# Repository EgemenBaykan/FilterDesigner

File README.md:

<h1><b>Filter Designer</b></h1>

<p>Filter Designer is a console program that designs 4 basic filters for given inputs. It is written in Python and Jupyter Notebook will be available soon. It is not recommended to use frequencies above 200-300 MHz since wavelength decreases in lumped element model filters. Use distributed element model for higher frequencies.</p>

<p>Filters are circuits that can pass or stop given frequencies or frequency bands. Passive filters contain passive elements unlike active filters. These elements are resistors, capacitors and inductors. Resistor is not a good practice in RF circuits. Therefore inductors are used instead of resistors since they boost the current.</p>

<p>In practice, passive filters are designed by using <b>Normalized Filter Coefficient Tables</b>. Filter order and characteristic are determined by performance requirements. This is, usually, done by providing attenuation on unwanted frequency components. Bode plots are used to analyze frequency response of RF circuits such as filters and magnitude is in <b>Decibel (dB)</b> scale.</p>

<h3><b>Program Inputs</b></h3>

<p> Basically there are 5 types of program inputs. These inputs are explained as follow:</p>

<ol>
    <li> <b>Filter Type:</b> </li>
    <ul>
        <li><b>LPF:</b> Defines Low Pass Filter.</li>
        <li><b>HPF:</b> Defines High Pass Filter.</li>
        <li><b>BPF:</b> Defines Band Pass Filter.</li>
        <li><b>BSF:</b> Defines Band Stop Filter.</li>
    </ul>
    <li> <b>Cutoff Frequency:</b> Defines -3dB point(s) of the filter. Low and high cutoff frequencies are given as inputs for Bandpass Filter or Bandstop Filter. Scientific notation is used for cutoff frequencies in Hz.</li>
    <li> <b>Filter Characteristic:</b> Defines filter characteristics to calculate zeros and poles. Only <b>Butterworth</b> and <b>Chebyshev</b> filters are available. Bessel response will be implemented in further updates.</li>
    <li> <b>Impedance:</b> Filter impedance. Typically 50 ohms. It is considered as source impedance is equal to load impedance in calculations. For impedance matching networks see Impedance Matching calculation tool repo.</li>
    <li> <b>Filter Order:</b> Filter order directly effects Transfer Function of the circuit in analysis. It's also can be obtained by number of delay elements of a circuit as seen in Finite Impulse Response (FIR) filter designs. </li>
</ol>

<h3><b>Program Outputs</b></h3>

<p> Filter coefficients, capacitor and inductor values are given as outputs at then end of program. Scientific notation is used for values of capacitors and inductors. All arrays are printed to console.
</p>

<h2> How to design a filter using Filter Designer?</h2>

<p> <b>It's strictly recommended to simulate the circuit by obtained values in filter topologies.</b> Run the program in the console and make an AC Analysis in <b>LTSpice</b> in order to analyze <b>Frequency Response</b> for obtained circuit. All the tests are done by simulation and few of obtained circuits are built on PCB's. Use a <b>Vector Network Analyzer (VNA)</b> for measurements on real PCB's. <b>S21</b> parameters on VNA must be matched with simulations.</p>
<p> Some of the simulations and measurements are given in following images.</p>

<p> Circuit topologies for High Pass and Low Pass Filters can be seen in image. Each circuit is labeled by its type, characteristic and cutoff frequency.</p>

<p> Simulation outputs can be observed as following for given generated circuits. Butterworth Low Pass Filter output is plotted in blue color. Butterworth and Chebyshev High Pass Filters are plotted in red and cyan colors.</p>

<p>For Bandstop Filter type simulation results may not be satisfying for good performance over attenuating the band. Transition width may need to be improved. Constructed circuit in LTSpice and simulation output is given as following.</p>

</img>

</img>

<p>Using circuit topologies in Filter_Simulations.asc file will be practical. Pi filter topology is used in this filter simulation file. Kicad files for given circuit topologies can be found in Kicad folder. GERBER files can be directly loaded to a PCB manufacturer. These circuits are designed by using 0603 / 1608 (metric) components. Therefore, power will be limited.</p>

<h2> References </h2>
<ol>
    <li> WINDER, S., Analog and Digital Filter Design.</li>
</ol>

<h3> Upcoming Updates </h3>
<ul> 
    <li>Getopt structure will be implemented.</li>
    <li>AC Analysis will be implemented. Simulation will be integrated within single script.</li>
    <li>User Interface may be implemented.</li>
</ul>

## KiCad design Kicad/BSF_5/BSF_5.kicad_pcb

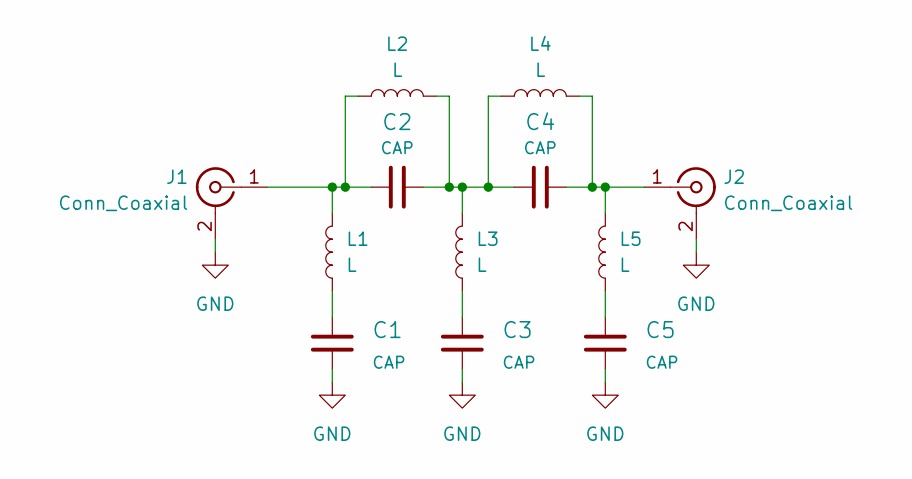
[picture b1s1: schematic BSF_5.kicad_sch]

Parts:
C1, C2, C3, C4, C5: CAP; C_0603_1608Metric
J1, J2: Conn_Coaxial; SMA_Amphenol_132289_EdgeMount
L1, L2, L3, L4, L5: L; L_0603_1608Metric

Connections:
GND: C1.2, C3.2, C5.2, J1.2 (Ext), J2.2 (Ext)
unnamed: C2.2, J1.1 (In), L1.2, L2.1
unnamed: C4.1, J2.1 (In), L4.2, L5.2
unnamed: C1.1, L1.1
unnamed: C2.1, C4.2, L2.2, L3.2, L4.1
unnamed: C3.1, L3.1
unnamed: C5.1, L5.1

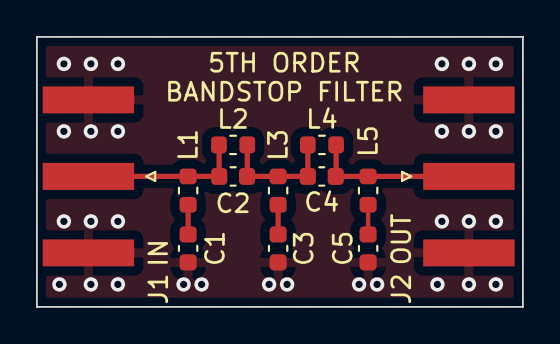
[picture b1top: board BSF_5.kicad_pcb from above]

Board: 4 copper layers, 27.0 x 15.0 mm, 12 parts (0 on the bottom side), 7 nets.

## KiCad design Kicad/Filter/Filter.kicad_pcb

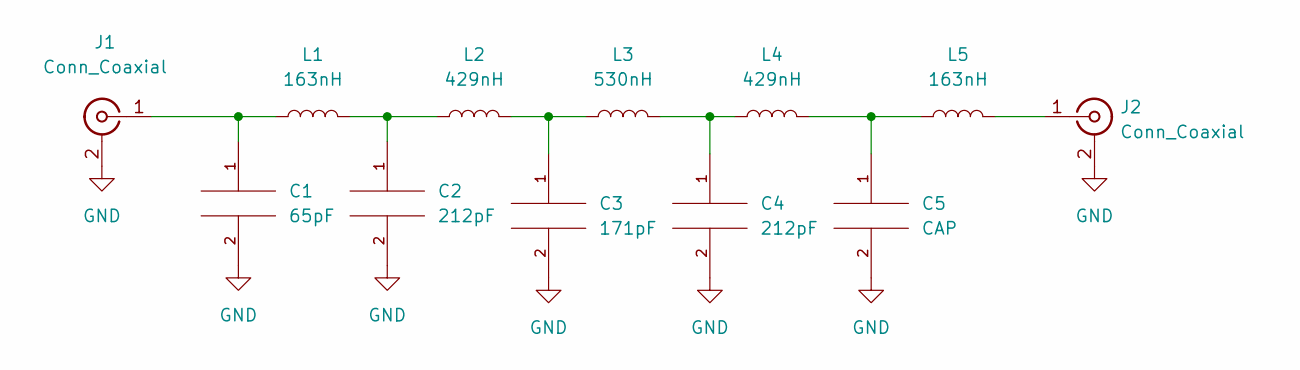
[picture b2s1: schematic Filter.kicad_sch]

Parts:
C1: 65pF; C_0805_2012Metric_Pad1.18x1.45mm_HandSolder
C2, C4: 212pF; C_0805_2012Metric_Pad1.18x1.45mm_HandSolder
C3: 171pF; C_0805_2012Metric_Pad1.18x1.45mm_HandSolder
C5: CAP; C_0805_2012Metric_Pad1.18x1.45mm_HandSolder
J1, J2: Conn_Coaxial; SMA_Amphenol_132289_EdgeMount
L1, L5: 163nH; L_0805_2012Metric_Pad1.05x1.20mm_HandSolder
L2, L4: 429nH; L_0805_2012Metric_Pad1.05x1.20mm_HandSolder
L3: 530nH; L_0805_2012Metric_Pad1.05x1.20mm_HandSolder

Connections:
GND: C1.2, C2.2, C3.2, C4.2, C5.2, J1.2 (Ext), J2.2 (Ext)
unnamed: C1.1, J1.1 (In), L1.1
unnamed: C3.1, L2.2, L3.1
unnamed: C4.1, L3.2, L4.1
unnamed: C5.1, L4.2, L5.1
unnamed: C2.1, L1.2, L2.1
unnamed: J2.1 (In), L5.2

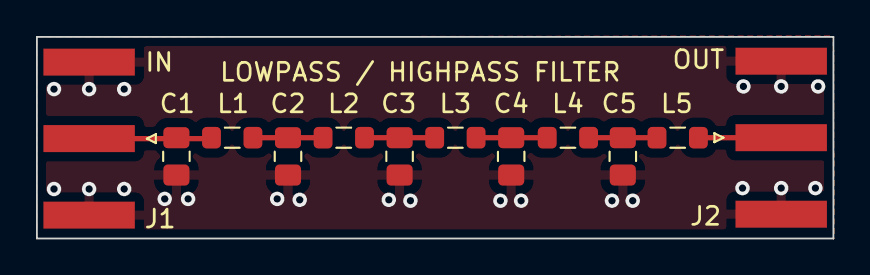
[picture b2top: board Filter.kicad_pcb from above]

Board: 4 copper layers, 44.2 x 11.2 mm, 12 parts (0 on the bottom side), 7 nets.

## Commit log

2023-04-27 Add files via upload
    Class structure implemented.
2023-05-03 Bandstop Filter added.
    Bandstop Filter design feature is added. Giving results may need to be improved.
2023-05-03 Update README.md
    Bandstop filter is implemented. Simulation results will be published.
2023-05-28 Add files via upload
    Added LTSpice simulations for filters with topologies.
2023-05-28 Update Band Stop Filter.
    Topology and simulation is changed.
